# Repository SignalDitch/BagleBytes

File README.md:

# BagleBytes
Toaster Oven controllers for solder reflow

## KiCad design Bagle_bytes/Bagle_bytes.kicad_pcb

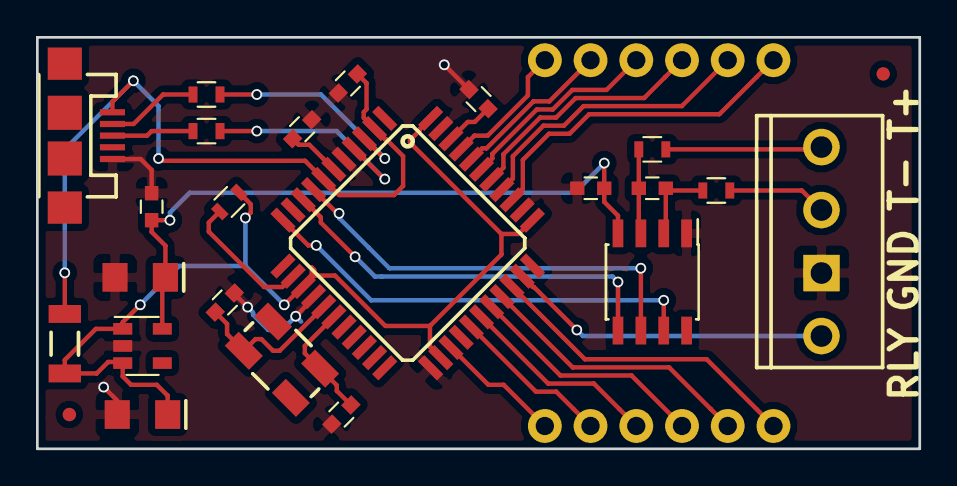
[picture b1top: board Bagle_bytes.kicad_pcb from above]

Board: 2 copper layers, 49.0 x 22.9 mm, 24 parts (0 on the bottom side), 34 nets.

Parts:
C1, C5, C8: 0.1UF-0603-100V-10%; C_0603
C2, C3: 10UF-POLAR-EIA3216-16V-10%_TANT_; EIA3216
C4: 10NF-0603-50V-10%; C_0603
C6, C7: 1.0UF-0603-16V-10%; C_0603
C9, C10: 22PF-0603-50V-5%; C_0603
F1: PPTC_HALF-AMP; SPARKFUN-POWERIC_PTC-1206-WIDE
FB1, FB2: FERRITE_BEAD-0603; L_0603
J1, J3: CONN_06NO_SILK_FEMALE_PTH; 1X06_NO_SILK
J2: CONN_04SCREW; SCREWTERMINAL-3.5MM-4
J4: USB_MICRO-B_SMT; USB-MICROB
M1: ATMEGA32U4TQFP-44; TQFP44
R1, R2: 22OHM-0603-1_10W-1%; R_0603
R3: 10KOHM-0603-1_10W-1%; R_0603
U1: MAX31855KASA; SOIC-8_3.9x4.9mm_Pitch1.27mm
U2: MIC5219-3.3BM5; SOT-23-5
Y1: CRYSTAL-16MHZSMD-5X3.2; CRYSTAL-SMD-5X3.2-4PAD

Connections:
3.3V: C1.1, C3.+, C5.1, U1.4, U2.5
5V: C2.+, F1.2, M1.14, M1.24, M1.34, M1.44, R3.1, U2.1, U2.3
/A0: J3.6, M1.36
/A1: J3.5, M1.37
/A2: J3.4, M1.38
/A3: J3.3, M1.39
/A4: J3.2, M1.40
/A5: J3.1, M1.41
/D4: J1.6, M1.25
/D5: J1.1, M1.31
/D6: J1.5, M1.27
/D8: J1.4, M1.28
/D9: J1.3, M1.29
/D10: J1.2, M1.30
/D+: M1.4, R1.2
/D-: M1.3, R2.2
/MISO: M1.11, U1.7
/RELAY: J2.4, M1.32
/SCK: M1.9, U1.5
/SS: M1.8, U1.6
/T+: C4.2, FB1.1, U1.3
/T-: C4.1, FB2.1, U1.2
/TIN+: FB1.2, J2.1
/TIN-: FB2.2, J2.2
/UVCC: C7.1, F1.1, J4.VBUS, M1.2, M1.7
GND: C1.2, C2.-, C3.-, C5.2, C6.2, C7.2, C8.2, C9.2, C10.2, J2.3, J4.GND, M1.5, M1.15, M1.23, M1.35, M1.43, U1.1, U2.2
unnamed: C6.1, M1.6
unnamed: C8.1, M1.42
unnamed: C9.1, M1.17, Y1.1
unnamed: C10.1, M1.16, Y1.3
unnamed: J4.D+, R1.1
unnamed: J4.D-, R2.1
unnamed: J4.MT1, J4.MT2, J4.P$1, J4.P$2
unnamed: M1.13, R3.2

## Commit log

2017-11-20 Results of 11/19 Stream
    Laid out the board and the panel. Gerbers are off to China
2017-11-22 New Panelizations
    Keeping the toaster oven width but going to single row panels.
